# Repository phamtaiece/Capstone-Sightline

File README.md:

Hello everyone, 
This Github is for our capstone project " Plug and Play Visual Landing Aid Accessory for UAVs." 

Let's have fun together.

              ********************************************************************************************
04/03/2019

Kimball will have a meeting with Sightline hardware team to discuss about the layout and make some adjustments. We expect to have a physical board soon.

Tai will work on the test plan for circuit board, clean and update the Github site. 

There are some changes in plan that we decided to change to Mission Planner and use flight simulation rather than physical quadcopter. Then, we will try use SLA-1500 hardware to communicate with the simulation model using serial communication.

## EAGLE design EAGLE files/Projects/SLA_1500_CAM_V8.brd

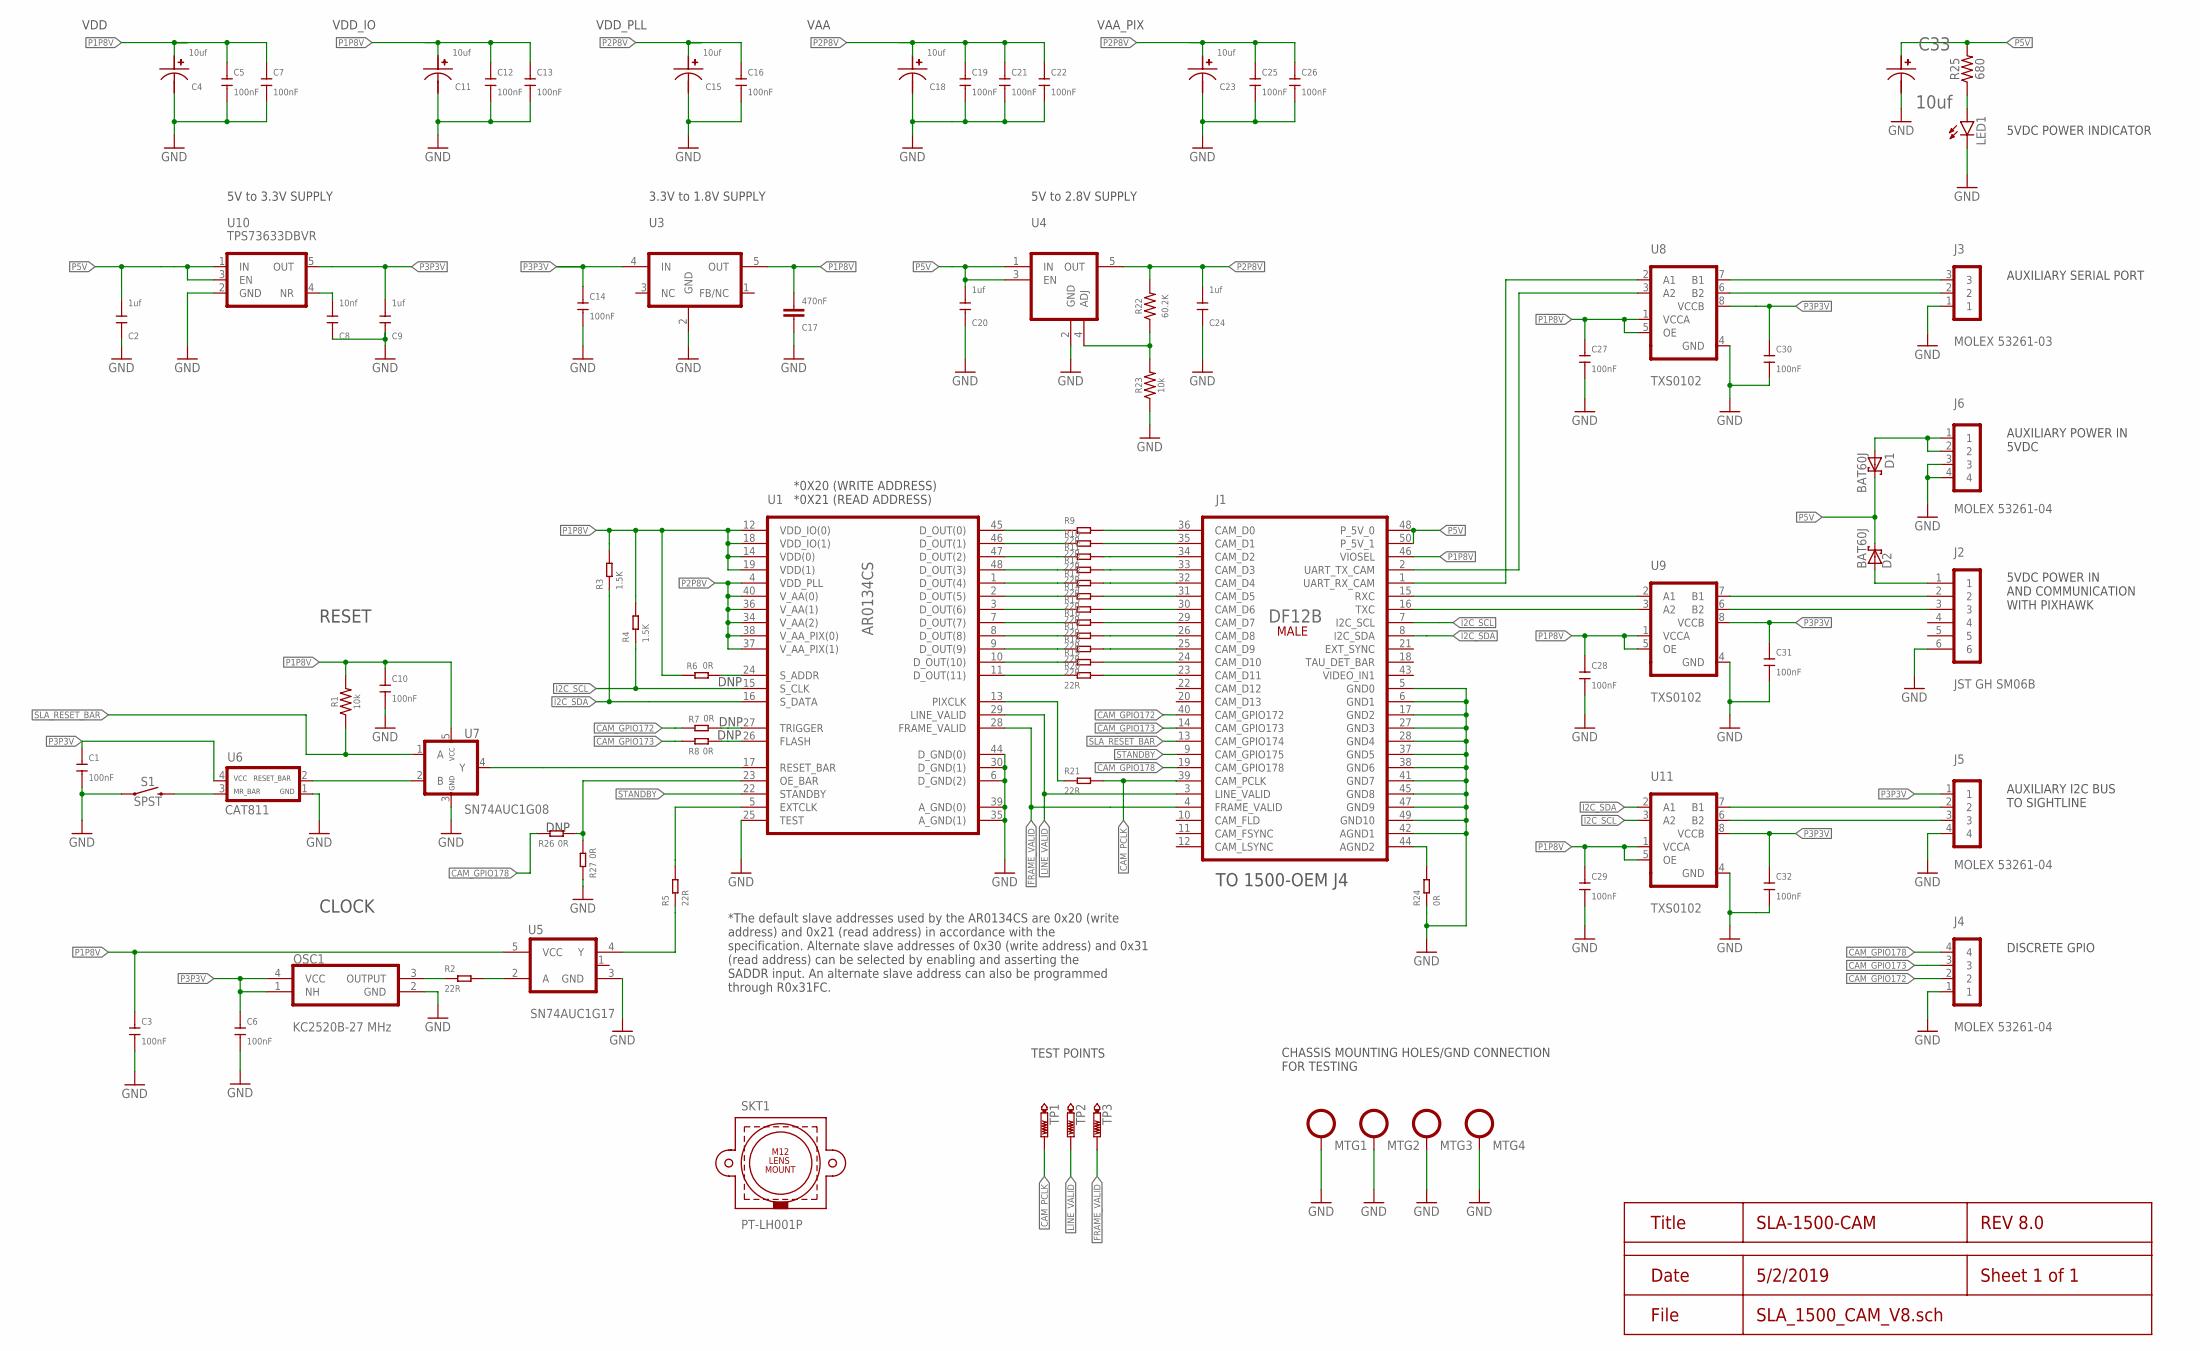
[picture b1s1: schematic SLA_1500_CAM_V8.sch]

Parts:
C1, C3, C5, C6, C7, C10, C12, C13, C14, C16, C19, C21, C22, C25, C26, C27, C28, C29, C30, C31, C32: 100nF; C0402
C2, C9, C20, C24: 1uf; C0402
C4, C11, C15, C18, C23, C33: 10uf; 0402
C8: 10nf; C0402
C17: 470nF; 0402
D1, D2: BAT60J; SOD323_ST
J1: DF12B(5.0)-50DS-0.5(86)SMT; DF12B(5.0)-50DS-0.5V(86)
J2: JST GH SM06B; JST_SM06B-GHS-TB
J3: MOLEX 53261-03; 53261-03
J4, J5, J6: MOLEX 53261-04; 53261-04
LED1: LEDCHIP-LED0603; CHIP-LED0603
MTG1, MTG2, MTG3, MTG4: SLA_MOUNTING
OSC1: KC2520B-27MHZ; 2.5X2.0_SMDCRYSTAL
R1, R23: 10k; 0603
R2, R5, R9, R10, R11, R12, R13, R14, R15, R16, R17, R18, R19, R20, R21: 22R; R0402
R3, R4: 1.5K; R0402
R6, R7, R8, R24, R26, R27: 0R; R0402
R22: 60.2K; 0603
R25: 680; 0603
S1: SPST; TACTILE_SWITCH_SMD_4.6X2.8MM
SKT1: PT-LH001P; M12_HOLDER
TP1, TP2, TP3: PTR1TP08SQ; TP08SQ
U1: AR0134CS-ILCC48; ILCC48_KD
U3: TPS71518DCKR; TI-SC70-5
U4: AP7331-WG-7; SOT-25
U5: SN74AUC1G17; SOT23-5
U6: CAT811; SOT-143-4
U7: SN74AUC1G08; SOT23-5
U8, U9, U11: TXS0102; X2SON(8)1.8X1.2MM
U10: TPS73633DBVR; SOT23-5

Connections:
CAM_GPIO172: J1.40 (CAM_GPIO172), J4.2, R7.2
CAM_GPIO173: J1.14 (CAM_GPIO173), J4.3, R8.2
CAM_GPIO178: J1.19 (CAM_GPIO178), J4.4, R26.2
CAM_PCLK: J1.39 (CAM_PCLK), R21.2, TP1.TP
FRAME_VALID: J1.4 (FRAME_VALID), TP3.TP, U1.28 (FRAME_VALID)
GND: C1.1, C2.1, C3.1, C4.2, C5.1, C6.1, C7.1, C8.1, C9.1, C10.1, C11.2, C12.1, C13.1, C14.1, C15.2, C16.1, C17.2, C18.2, C19.1, C20.1, C21.1, C22.1, C23.2, C24.1, C25.1, C26.1, C27.1, C28.1, C29.1, C30.1, C31.1, C32.1, C33.2, J1.5 (GND0), J1.6 (GND1), J1.17 (GND2), J1.27 (GND3), J1.28 (GND4), J1.37 (GND5), J1.38 (GND6), J1.41 (GND7), J1.42 (AGND1), J1.45 (GND8), J1.47 (GND9), J1.49 (GND10), J2.6, J3.1, J4.1, J5.4, J6.3, J6.4, LED1.C, MTG1.P$1, MTG2.P$1, MTG3.P$1, MTG4.P$1, OSC1.2 (GND), R23.1, R24.1, R27.2, S1.1, S1.2 (1), U1.6 (D_GND(2)), U1.25 (TEST), U1.30 (D_GND(1)), U1.35 (A_GND(1)), U1.39 (A_GND(0)), U1.44 (D_GND(0)), U3.2 (GND), U4.2 (GND), U5.3 (GND), U6.1 (GND), U7.3 (GND), U8.4 (GND), U9.4 (GND), U10.2 (GND), U11.4 (GND)
I2C_SCL: J1.7 (I2C_SCL), R4.1, U1.15 (S_CLK), U11.3 (A2)
I2C_SDA: J1.8 (I2C_SDA), R3.1, U1.16 (S_DATA), U11.2 (A1)
LINE_VALID: J1.3 (LINE_VALID), TP2.TP, U1.29 (LINE_VALID)
unnamed: J2.3, U9.6 (B2)
unnamed: R9.1, U1.45 (D_OUT(0))
unnamed: J1.36 (CAM_D0), R9.2
unnamed: R10.1, U1.46 (D_OUT(1))
unnamed: J1.35 (CAM_D1), R10.2
unnamed: R11.1, U1.47 (D_OUT(2))
unnamed: J1.34 (CAM_D2), R11.2
unnamed: R12.1, U1.48 (D_OUT(3))
unnamed: J1.33 (CAM_D3), R12.2
unnamed: R13.1, U1.1 (D_OUT(4))
unnamed: J1.32 (CAM_D4), R13.2
unnamed: R14.1, U1.2 (D_OUT(5))
unnamed: J3.3, U8.7 (B1)
unnamed: J1.31 (CAM_D5), R14.2
unnamed: R2.2, U5.2 (A)
unnamed: OSC1.3 (OUTPUT), R2.1
unnamed: J2.2, U9.7 (B1)
unnamed: J3.2, U8.6 (B2)
unnamed: J1.1 (UART_RX_CAM), U8.2 (A1)
unnamed: J1.2 (UART_TX_CAM), U8.3 (A2)
unnamed: C8.2, U10.4 (NR)
unnamed: R15.1, U1.3 (D_OUT(6))
unnamed: R22.1, R23.2, U4.4 (ADJ)
unnamed: J1.30 (CAM_D6), R15.2
unnamed: R5.1, U5.4 (Y)
unnamed: R5.2, U1.5 (EXTCLK)
unnamed: S1.3 (2), S1.4 (2), U6.3 (MR_BAR)
unnamed: U6.2 (RESET_BAR), U7.2 (B)
unnamed: U1.17 (RESET_BAR), U7.4 (Y)
unnamed: LED1.A, R25.1
unnamed: J1.44 (AGND2), R24.2
unnamed: R7.1, U1.27 (TRIGGER)
unnamed: R8.1, U1.26 (FLASH)
unnamed: D2.A, J2.1
unnamed: J1.15 (RXC), U9.2 (A1)
unnamed: J1.16 (TXC), U9.3 (A2)
unnamed: J5.2, U11.7 (B1)
unnamed: J5.3, U11.6 (B2)
unnamed: D1.A, J6.1, J6.2
unnamed: R16.1, U1.7 (D_OUT(7))
unnamed: J1.29 (CAM_D7), R16.2
unnamed: R17.1, U1.8 (D_OUT(8))
unnamed: J1.26 (CAM_D8), R17.2
unnamed: R18.1, U1.9 (D_OUT(9))
unnamed: J1.25 (CAM_D9), R18.2
unnamed: R19.1, U1.10 (D_OUT(10))
unnamed: J1.24 (CAM_D10), R19.2
unnamed: R20.1, U1.11 (D_OUT(11))
unnamed: J1.23 (CAM_D11), R20.2
unnamed: R26.1, R27.1, U1.23 (OE_BAR)
unnamed: R6.1, U1.24 (S_ADDR)
P1P8V: C3.2, C4.1, C5.2, C7.2, C10.2, C11.1, C12.2, C13.2, C17.1, C27.2, C28.2, C29.2, J1.46 (VIOSEL), R1.2, R3.2, R4.2, R6.2, U1.12 (VDD_IO(0)), U1.14 (VDD(0)), U1.18 (VDD_IO(1)), U1.19 (VDD(1)), U3.5 (OUT), U5.5 (VCC), U7.5 (VCC), U8.1 (VCCA), U8.5 (OE), U9.1 (VCCA), U9.5 (OE), U11.1 (VCCA), U11.5 (OE)
P2P8V: C15.1, C16.2, C18.1, C19.2, C21.2, C22.2, C23.1, C24.2, C25.2, C26.2, R22.2, U1.4 (VDD_PLL), U1.34 (V_AA(2)), U1.36 (V_AA(1)), U1.37 (V_AA_PIX(1)), U1.38 (V_AA_PIX(0)), U1.40 (V_AA(0)), U4.5 (OUT)
P3P3V: C1.2, C6.2, C9.2, C14.2, C30.2, C31.2, C32.2, J5.1, OSC1.1 (NH), OSC1.4 (VCC), U3.4 (IN), U6.4 (VCC), U8.8 (VCCB), U9.8 (VCCB), U10.5 (OUT), U11.8 (VCCB)
P5V: C2.2, C20.2, C33.1, D1.C, D2.C, J1.48 (P_5V_0), J1.50 (P_5V_1), R25.2, U4.1 (IN), U4.3 (EN), U10.1 (IN), U10.3 (EN)
PIXCLK: R21.1, U1.13 (PIXCLK)
SLA_RESET_BAR: J1.13 (CAM_GPIO174), R1.1, U7.1 (A)
STANDBY: J1.9 (CAM_GPIO175), U1.22 (STANDBY)

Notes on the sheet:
AUXILIARY POWER IN 5VDC
AUXILIARY I2C BUS TO SIGHTLINE
DISCRETE GPIO
5VDC POWER IN AND COMMUNICATION WITH PIXHAWK
AUXILIARY SERIAL PORT
5V to 3.3V SUPPLY
3.3V to 1.8V SUPPLY
5V to 2.8V SUPPLY
TO 1500-OEM J4
DNP
5VDC POWER INDICATOR
*The default slave addresses used by the AR0134CS are 0x20 (write address) and 0x21 (read address) in accordance with the specification. Alternate slave addresses of 0x30 (write address) and 0x31 (read address) can be selected by enabling and asserting the SADDR input. An alternate slave address ca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
*0X20 (WRITE ADDRESS) *0X21 (READ ADDRESS)
CHASSIS MOUNTING HOLES/GND CONNECTION FOR TESTING
TEST POINTS
CLOCK
RESET
VDD
VDD_PLL
VAA
VAA_PIX
VDD_IO

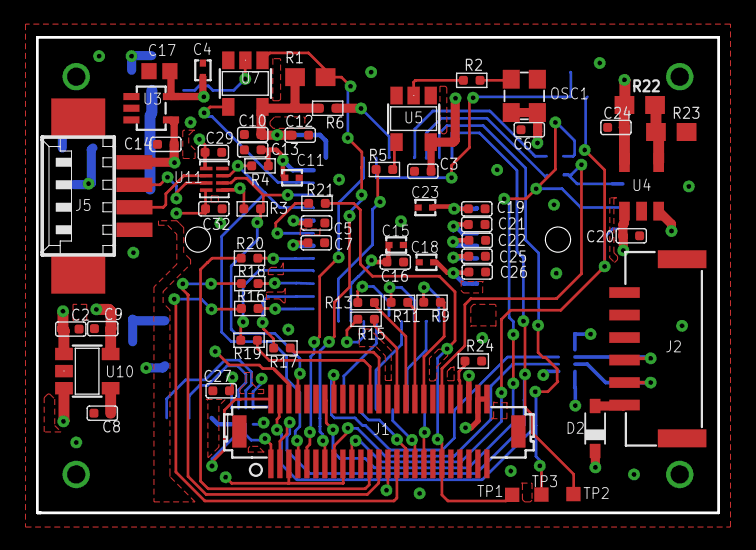
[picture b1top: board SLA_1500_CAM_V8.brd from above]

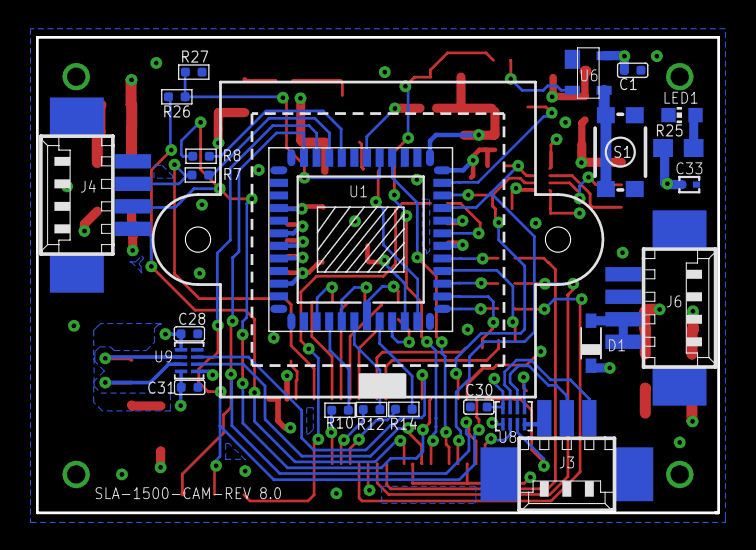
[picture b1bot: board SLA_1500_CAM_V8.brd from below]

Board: 4 copper layers, 37.8 x 26.4 mm, 89 parts (24 on the bottom side), 67 nets.

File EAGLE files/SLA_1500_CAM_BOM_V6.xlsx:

Qty | Value | Device | Package | Parts | Description | DESCRIPTION.1 | MANF | MANF# | MPN | PROD_ID | TP_SIGNAL_NAME | VALUE.1 | Column1
1 |  | AP7331-WG-7 | SOT-25 | U4 | AP7331-WG-7 | 300mA, LOW QUIESCENT CURRENT, FAST TRANSIENT LOW DROPOUT LINEAR REGULATOR, ADJU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 | DIODES INCORPORATED | AP7331-WG-7
1 |  | AR0134CS-ILCC48 | ILCC48_KD | U1 | AR0134CS-1LCC48-10x10 | 1/3-inch 1.2 Mp CMOS digital image sensor with an active-pixel array of 1280 (H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 | On Semiconductor | AR0134CSSM00SPCA0
1 |  | CAT811 | SOT-143-4 | U6 | CAT811-SOT-143-4 | IC, SUPERVISOR, MICROPROCESSOR POWER SUPPLY, 2.93V, ACTIVE LOW RESET, SOT143-4 | On Semiconductor | CAT811STBI
1 |  | DF12B(5.0)-50DS-0.5(86)SMT | DF12B(5.0)-50DS-0.5V(86) | J1 | DF12B(5.0)-50DS-0.5(86) | DF12B-50DS-0.5V(86) Hirose Male 50-pin connector | Hirose | 537-0309-6 86
1 |  | KC2520B-27MHZ | 2.5X2.0_SMDCRYSTAL | OSC1 | KC2520B-27MHz-2.5X2.0 | OSC, CRYSTAL CLOCK, SMD, CMOS, 2.25V TO 3.63V, 4mA, 27.0000MHz, 2.5MM x 2.0MM | Kyocera | KC2520B27.0000C2GE00
1 |  | LEDCHIP-LED0603 | CHIP-LED0603 | LED1 | LED
4 |  | SLA_MOUNTING | SLA_MOUNTING | MTG1, MTG2, MTG3, MTG4
1 |  | SN74AUC1G08 | SOT23-5 | U7 | SN74AUC1G08-SOT23-5 | IC, AND GATE, SINGLE, 2 INPUT POSITIVE, SGL, SOT23-5 | Texas Instruments | SN74AUC1G08DBVR
1 |  | SN74AUC1G17 | SOT23-5 | U5 | SN74AUC1G17-SOT23-5 | IC, BUFFER, SINGLE SCHMITT-TRIGGER, 9mA, 0.8V TO 2.7V, SOT23-5 | TEXAS INSTRUMENTS | SN74AUC1G17DBV
1 |  | TPS71518DCKR | TI-SC70-5 | U3 | TPS71518DCKR | 50-mA, 24-V, 3.2-Î¼A Supply Current Low-Dropout Linear Regulator in SC70 5-Pin 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 | TEXAS INSTRUMENTS | TPS71518DCKR
4 | 0R | SMD-RES-0R-5%-1/16W(0402) | R0402 | R6, R7, R8, R24 | 301010000 |  |  |  | RC0402JR-070RL |  |  | 0R
2 | 1.5K | SMD-RES-1.5K-5%-1/16W(0402) | R0402 | R3, R4 | 301010001 |  |  |  | RC0402JR-071K5L |  |  | 1.5K
21 | 100nF | CERAMICÂ 100NF-10V-10%-X5R(0402) | C0402 | C1, C3, C5, C6, C7, C10, C12, C13, C14, C16, C19, C21, C22, C25, C26, C27, C28,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 | 302010037 |  |  |  | CC0402KRX5R6BB104 |  |  | 100NF 10V
2 | 10k | 10KOHM-0603-1/10W-1% | 0603 | R1, R23 | 10kÎ© resistor |  |  |  |  | RES-00824 |  | 10k
1 | 10nf | CERAMIC-10NF-50V-10%-X7R(0402) | C0402 | C8 | 302010006 |  |  |  | CC0402KRX7R9BB103 |  |  | 10nf
5 | 10uf | F980G106MUA | 0402 | C4, C11, C15, C18, C23 | F980G106MUA | Tantalum Capacitors - Solid SMD 10uF 4V 20% 0402, 1.1x0.6x0.35mm | AVX | F980G106MUA
1 | 10uf | F980J106MUALZT | 0402 | C33 | F980G106MUALZT | Tantalum Capacitors - Solid SMD 10uF 6.3V 20% 0402, 1.1x0.6x0.35mm | AVX | F980J106MUALZT
4 | 1uf | CERAMIC-1UF-10V-10%-X5R(0402) | C0402 | C2, C9, C20, C24 | 302010040 |  |  |  | CC0402KRX5R6BB105 |  |  | 1uf
15 | 22R | SMD-RES-22R-1%-1/16W(0402) | R0402 | R2, R5, R9, R10, R11, R12, R13, R14, R15, R16, R17, R18, R19, R20, R21 | 301010052 |  |  |  | RC0402FR-0722RL |  |  | 22R
1 | 470nF | 470NF-0402-16V-10% | 0402 | C17 | 0.47uF/470nF ceramic capacitors |  |  |  |  | CAP-09041 |  | 470nF
1 | 60.2K | 62KOHM-0603-1/10W-5% | 0603 | R22 | 62kÎ© resistor
1 | 680 | 680OHM-0603-1/10W-5% | 0603 | R25 | 680Î© resistor |  |  |  |  | RES-09333 |  | 680
2 | BAT60J | BAT60J | SOD323_ST | D1, D2 | Schottky barrier diode
1 | JST GH SM06B | JST_GH_SM06B-GHS-TB | JST_SM06B-GHS-TB | J2 | JST SM06B-GHS-TB | 1.25 MM SIDE-ENTRY 6-PIN SMT CONNECTOR | JST | SM06B-GHS-TB
1 | MOLEX 53261-03 | MOLEX53261-03 | 53261-03 | J3 | MOLEX 53261-03 | 1.25mm Pitch PicoBlade Header, Surface Mount, Right-Angle, 3 Circuits, Tin (Sn)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 | MOLEX | 532610371
3 | MOLEX 53261-04 | MOLEX53261-04 | 53261-04 | J4, J5, J6 | MOLEX 53261-04 | 1.25mm Pitch PicoBlade Header, Surface Mount, Right-Angle, 4 Circuits, Tin (Sn)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 | MOLEX | 532610471
1 | PT-LH001P | M12_LENS_MOUNT | M12_HOLDER | SKT1 | PT-LH001P | PT-LH001P Plastic M12 Lens Holder, 20mm Hole Spacing | M12 LENSES | PT-LH001P
3 | PTR1TP08SQ | PTR1TP08SQ | TP08SQ | TP1, TP2, TP3 | TEST PIN
1 | SPST | MOMENTARY-SWITCH-SPST-SMD-4.6X2.8MM | TACTILE_SWITCH_SMD_4.6X2.8MM | S1 | Momentary Switch (Pushbutton) - SPST |  |  |  |  | SWCH-13065
1 | TPS73633DBVR | TPS73633DBVR | SOT23-5 | U10 | TPS73633DBVR | Cap-Free, NMOS, 400-mA Low-Dropout Regulator with Reverse Current Protection 5.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 | Texas Instruments | TPS73633DBVR
3 | TXS0102 | TXS0102DQM | X2SON(8)1.8X1.2MM | U8, U9, U11 | TXS0102DQM 1.8 X 1.2 mm | TXS0102 2-Bit Bidirectional Voltage-Level Translator for Open-Drain and Push-Pu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 | Texas Instruments | TXS0102DQM

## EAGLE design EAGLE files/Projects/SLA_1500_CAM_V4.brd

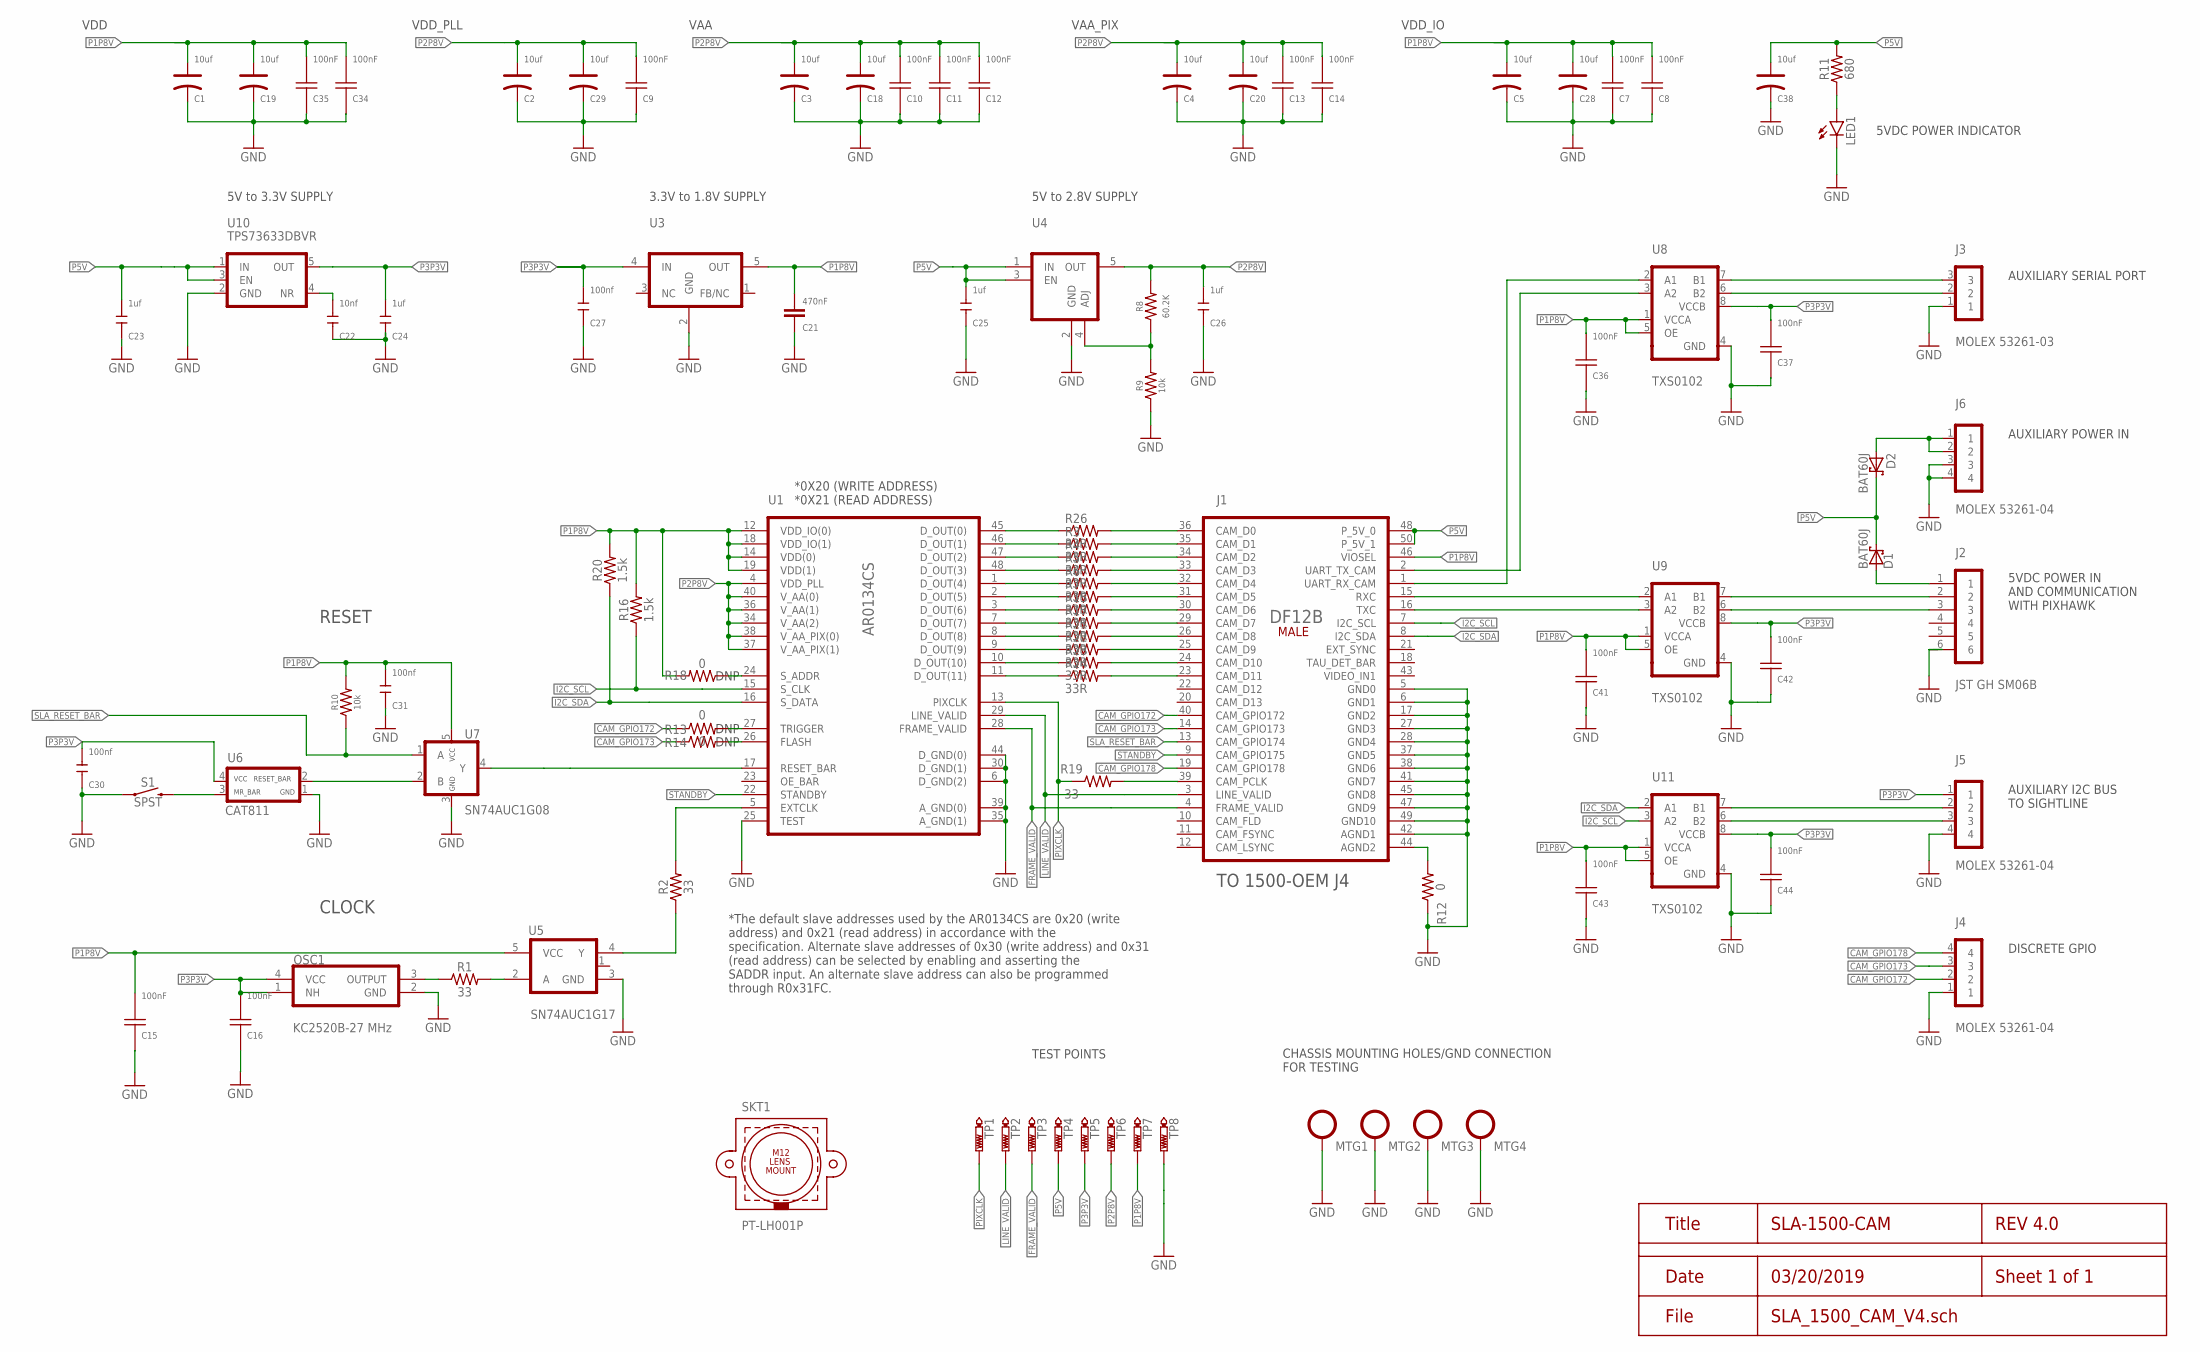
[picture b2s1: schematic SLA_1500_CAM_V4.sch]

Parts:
C1, C2, C3, C4, C5, C18, C19, C20, C28, C29, C38: 10uf; AVX-A
C7, C8, C9, C10, C11, C12, C13, C14, C15, C16, C34, C35, C36, C37, C41, C42, C43, C44: CAP0201100NF; R0201
C21: 470nF; 0402
C22: 10nf; C0402
C23, C24, C25, C26: 1uf; C0402
C27, C30, C31: 100nf; C0402
D1, D2: BAT60J; SOD323_ST
J1: DF12B(5.0)-50DS-0.5(86)SMT; DF12B(5.0)-50DS-0.5V(86)
J2: JST GH SM06B; JST_SM06B-GHS-TB
J3: MOLEX 53261-03; 53261-03
J4, J5, J6: MOLEX 53261-04; 53261-04
LED1: LEDCHIP-LED0603; CHIP-LED0603
MTG1, MTG2, MTG3, MTG4: SLA_MOUNTING
OSC1: KC2520B-27MHZ; 2.5X2.0_SMDCRYSTAL
R1, R2, R19: 33; 0402
R3, R4, R5, R6, R7, R15, R17, R21, R22, R23, R24, R26: 33R; R0201
R8: 60.2K; 0603
R9, R10: 10k; 0603
R11: 680; 0603
R12, R13, R14, R18: 0; 0402
R16, R20: 1.5k; 0603
S1: SPST; TACTILE_SWITCH_SMD_4.6X2.8MM
SKT1: PT-LH001P; M12_HOLDER
TP1, TP2, TP3, TP4, TP5, TP6, TP7, TP8: PTR1PAD1-13; P1-13
U1: AR0134CS-ILCC48; ILCC48_KD
U3: TPS71518DCKR; TI-SC70-5
U4: AP7331-WG-7; SOT-25
U5: SN74AUC1G17; SOT23-5
U6: CAT811; SOT-143-4
U7: SN74AUC1G08; SOT23-5
U8, U9, U11: TXS0102; X2SON(8)1.8X1.2MM
U10: TPS73633DBVR; SOT23-5

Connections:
CAM_GPIO172: J1.40 (CAM_GPIO172), J4.2, R13.1
CAM_GPIO173: J1.14 (CAM_GPIO173), J4.3, R14.1
CAM_GPIO178: J1.19 (CAM_GPIO178), J4.4
FRAME_VALID: J1.4 (FRAME_VALID), TP3.TP, U1.28 (FRAME_VALID)
GND: C1.-, C2.-, C3.-, C4.-, C5.-, C7.2, C8.2, C9.2, C10.2, C11.2, C12.2, C13.2, C14.2, C15.2, C16.2, C18.-, C19.-, C20.-, C21.2, C22.1, C23.1, C24.1, C25.1, C26.1, C27.1, C28.-, C29.-, C30.1, C31.1, C34.2, C35.2, C36.2, C37.2, C38.-, C41.2, C42.2, C43.2, C44.2, J1.5 (GND0), J1.6 (GND1), J1.17 (GND2), J1.27 (GND3), J1.28 (GND4), J1.37 (GND5), J1.38 (GND6), J1.41 (GND7), J1.42 (AGND1), J1.45 (GND8), J1.47 (GND9), J1.49 (GND10), J2.6, J3.1, J4.1, J5.4, J6.3, J6.4, LED1.C, MTG1.P$1, MTG2.P$1, MTG3.P$1, MTG4.P$1, OSC1.2 (GND), R9.1, R12.1, S1.1, S1.2 (1), TP8.TP, U1.6 (D_GND(2)), U1.25 (TEST), U1.30 (D_GND(1)), U1.35 (A_GND(1)), U1.39 (A_GND(0)), U1.44 (D_GND(0)), U3.2 (GND), U4.2 (GND), U5.3 (GND), U6.1 (GND), U7.3 (GND), U8.4 (GND), U9.4 (GND), U10.2 (GND), U11.4 (GND)
I2C_SCL: J1.7 (I2C_SCL), R16.1, U1.15 (S_CLK), U11.3 (A2)
I2C_SDA: J1.8 (I2C_SDA), R20.1, U1.16 (S_DATA), U11.2 (A1)
LINE_VALID: J1.3 (LINE_VALID), TP2.TP, U1.29 (LINE_VALID)
unnamed: J2.3, U9.6 (B2)
unnamed: R26.1, U1.45 (D_OUT(0))
unnamed: J1.36 (CAM_D0), R26.2
unnamed: R3.1, U1.46 (D_OUT(1))
unnamed: J1.35 (CAM_D1), R3.2
unnamed: R4.1, U1.47 (D_OUT(2))
unnamed: J1.34 (CAM_D2), R4.2
unnamed: R5.1, U1.48 (D_OUT(3))
unnamed: J1.33 (CAM_D3), R5.2
unnamed: R6.1, U1.1 (D_OUT(4))
unnamed: J1.32 (CAM_D4), R6.2
unnamed: R7.1, U1.2 (D_OUT(5))
unnamed: J3.3, U8.7 (B1)
unnamed: J1.31 (CAM_D5), R7.2
unnamed: R1.2, U5.2 (A)
unnamed: OSC1.3 (OUTPUT), R1.1
unnamed: J2.2, U9.7 (B1)
unnamed: J3.2, U8.6 (B2)
unnamed: J1.1 (UART_RX_CAM), U8.2 (A1)
unnamed: J1.2 (UART_TX_CAM), U8.3 (A2)
unnamed: C22.2, U10.4 (NR)
unnamed: R15.1, U1.3 (D_OUT(6))
unnamed: R8.1, R9.2, U4.4 (ADJ)
unnamed: J1.30 (CAM_D6), R15.2
unnamed: R2.1, U5.4 (Y)
unnamed: R2.2, U1.5 (EXTCLK)
unnamed: S1.3 (2), S1.4 (2), U6.3 (MR_BAR)
unnamed: U6.2 (RESET_BAR), U7.2 (B)
unnamed: U1.17 (RESET_BAR), U7.4 (Y)
unnamed: LED1.A, R11.1
unnamed: J1.44 (AGND2), R12.2
unnamed: R13.2, U1.27 (TRIGGER)
unnamed: R14.2, U1.26 (FLASH)
unnamed: D1.A, J2.1
unnamed: J1.15 (RXC), U9.2 (A1)
unnamed: J1.16 (TXC), U9.3 (A2)
unnamed: J5.2, U11.7 (B1)
unnamed: J5.3, U11.6 (B2)
unnamed: D2.A, J6.1, J6.2
unnamed: R17.1, U1.7 (D_OUT(7))
unnamed: J1.29 (CAM_D7), R17.2
unnamed: R21.1, U1.8 (D_OUT(8))
unnamed: J1.26 (CAM_D8), R21.2
unnamed: R22.1, U1.9 (D_OUT(9))
unnamed: J1.25 (CAM_D9), R22.2
unnamed: R23.1, U1.10 (D_OUT(10))
unnamed: J1.24 (CAM_D10), R23.2
unnamed: R24.1, U1.11 (D_OUT(11))
unnamed: J1.23 (CAM_D11), R24.2
unnamed: R18.1, U1.24 (S_ADDR)
unnamed: J1.39 (CAM_PCLK), R19.2
P1P8V: C1.+, C5.+, C7.1, C8.1, C15.1, C19.+, C21.1, C28.+, C31.2, C34.1, C35.1, C36.1, C41.1, C43.1, J1.46 (VIOSEL), R10.2, R16.2, R18.2, R20.2, TP7.TP, U1.12 (VDD_IO(0)), U1.14 (VDD(0)), U1.18 (VDD_IO(1)), U1.19 (VDD(1)), U3.5 (OUT), U5.5 (VCC), U7.5 (VCC), U8.1 (VCCA), U8.5 (OE), U9.1 (VCCA), U9.5 (OE), U11.1 (VCCA), U11.5 (OE)
P2P8V: C2.+, C3.+, C4.+, C9.1, C10.1, C11.1, C12.1, C13.1, C14.1, C18.+, C20.+, C26.2, C29.+, R8.2, TP6.TP, U1.4 (VDD_PLL), U1.34 (V_AA(2)), U1.36 (V_AA(1)), U1.37 (V_AA_PIX(1)), U1.38 (V_AA_PIX(0)), U1.40 (V_AA(0)), U4.5 (OUT)
P3P3V: C16.1, C24.2, C27.2, C30.2, C37.1, C42.1, C44.1, J5.1, OSC1.1 (NH), OSC1.4 (VCC), TP5.TP, U3.4 (IN), U6.4 (VCC), U8.8 (VCCB), U9.8 (VCCB), U10.5 (OUT), U11.8 (VCCB)
P5V: C23.2, C25.2, C38.+, D1.C, D2.C, J1.48 (P_5V_0), J1.50 (P_5V_1), R11.2, TP4.TP, U4.1 (IN), U4.3 (EN), U10.1 (IN), U10.3 (EN)
PIXCLK: R19.1, TP1.TP, U1.13 (PIXCLK)
SLA_RESET_BAR: J1.13 (CAM_GPIO174), R10.1, U7.1 (A)
STANDBY: J1.9 (CAM_GPIO175), U1.22 (STANDBY)

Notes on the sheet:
AUXILIARY POWER IN
AUXILIARY I2C BUS TO SIGHTLINE
DISCRETE GPIO
5VDC POWER IN AND COMMUNICATION WITH PIXHAWK
AUXILIARY SERIAL PORT
5V to 3.3V SUPPLY
3.3V to 1.8V SUPPLY
5V to 2.8V SUPPLY
TO 1500-OEM J4
DNP
5VDC POWER INDICATOR
*The default slave addresses used by the AR0134CS are 0x20 (write address) and 0x21 (read address) in accordance with the specification. Alternate slave addresses of 0x30 (write address) and 0x31 (read address) can be selected by enabling and asserting the SADDR input. An alternate slave address ca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
*0X20 (WRITE ADDRESS) *0X21 (READ ADDRESS)
CHASSIS MOUNTING HOLES/GND CONNECTION FOR TESTING
TEST POINTS
CLOCK
RESET
VDD
VDD_PLL
VAA
VAA_PIX
VDD_IO

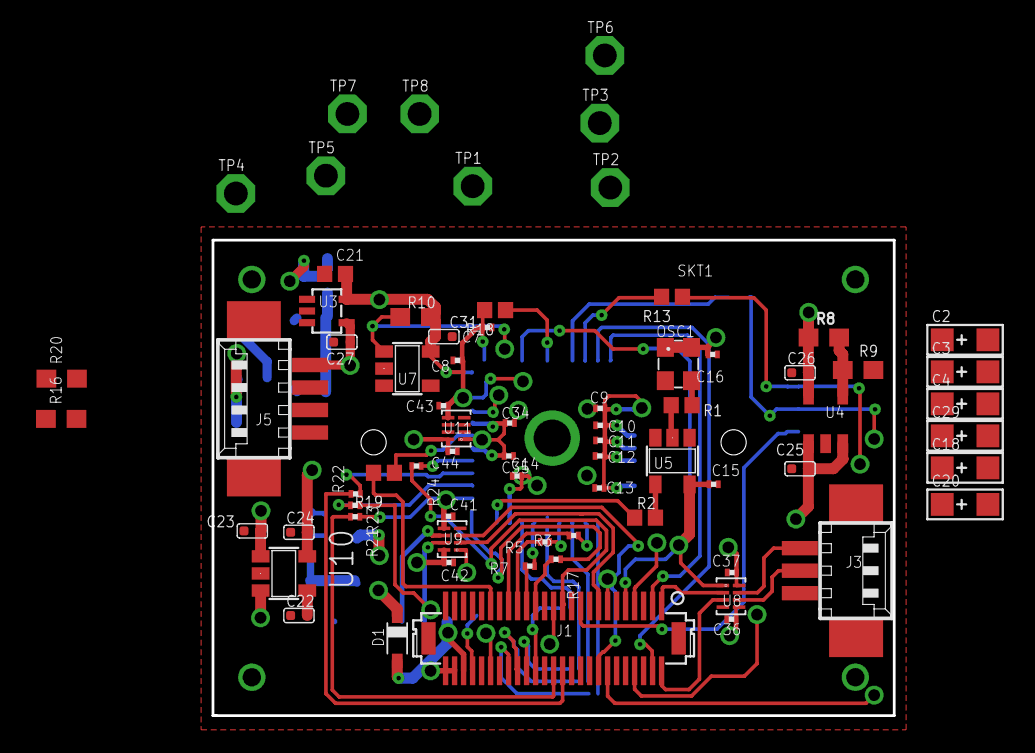
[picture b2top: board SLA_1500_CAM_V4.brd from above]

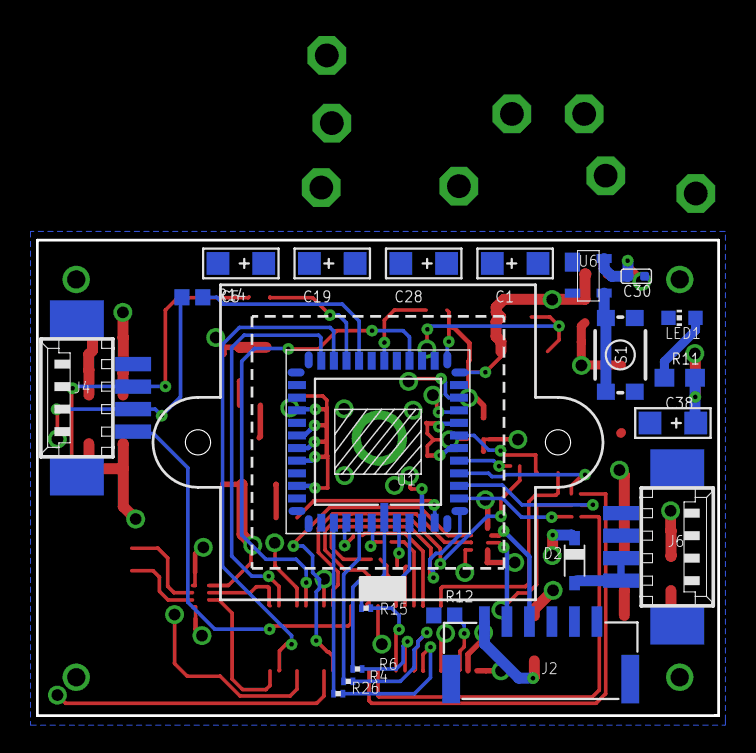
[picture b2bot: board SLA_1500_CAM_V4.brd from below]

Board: 4 copper layers, 37.8 x 26.4 mm, 97 parts (22 on the bottom side), 66 nets.

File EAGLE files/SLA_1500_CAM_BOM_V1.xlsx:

Qty | Value | Device | Package | Parts | Description | DESCRIPTION.1 | MANF | MANF# | MPN | PROD_ID | VALUE.1 | Column1
1 |  | AP7331-WG-7 | SOT-25 | U4 | AP7331-WG-7 | 300mA, LOW QUIESCENT CURRENT, FAST TRANSIENT LOW DROPOUT LINEAR REGULATOR, ADJU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 | DIODES INCORPORATED | AP7331-WG-7
1 |  | AR0134CS-ILCC48 | ILCC48 | U1 | AR0134CS-1LCC48-10x10 | 1/3-inch 1.2 Mp CMOS digital image sensor with an active-pixel array of 1280 (H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 | On Semiconductor | AR0134CSSM00SPCA0
1 |  | CAT811 | SOT-143-4 | U6 | CAT811-SOT-143-4 | IC, SUPERVISOR, MICROPROCESSOR POWER SUPPLY, 2.93V, ACTIVE LOW RESET, SOT143-4 | On Semiconductor | CAT811STBI
1 |  | DF12B(5.0)-50DS-0.5(86)SMT | DF12B(5.0)-50DS-0.5V(86) | J1 | DF12B(5.0)-50DS-0.5(86) | DF12B-50DS-0.5V(86) Hirose Male 50-pin connector | Hirose | 537-0309-6 86
1 |  | JST_GH_SM06B-GHS-TB | JST_SM06B-GHS-TB | J2 | JST SM06B-GHS-TB | 1.25 MM SIDE-ENTRY 6-PIN SMT CONNECTOR | JST | SM06B-GHS-TB
1 |  | KC2520B-27MHZ | 2.5X2.0_SMDCRYSTAL | OSC1 | KC2520B-27MHz-2.5X2.0 | OSC, CRYSTAL CLOCK, SMD, CMOS, 2.25V TO 3.63V, 4mA, 27.0000MHz, 2.5MM x 2.0MM | Kyocera | KC2520B27.0000C2GE00
1 |  | LEDCHIP-LED0603 | CHIP-LED0603 | LED1 | LED
1 |  | MOLEX_53048-03 | 53048-03 | J3 |  | MOLEX 53048-03 3-PIN CONNECTOR | MOLEX | 53048-0310
2 |  | MOLEX_53398-04 | 53398-04 | J4, J6 |  | MOLEX 53398-04 4-PIN SMT CONNECTOR | MOLEX | 53398-0471
1 |  | SN74AUC1G08 | SOT23-5 | U7 | SN74AUC1G08-SOT23-5 | IC, AND GATE, SINGLE, 2 INPUT POSITIVE, SGL, SOT23-5 | Texas Instruments | SN74AUC1G08DBVR
1 |  | SN74AUC1G17 | SOT23-5 | U5 | SN74AUC1G17-SOT23-5 | IC, BUFFER, SINGLE SCHMITT-TRIGGER, 9mA, 0.8V TO 2.7V, SOT23-5 | TEXAS INSTRUMENTS | SN74AUC1G17DBV
1 |  | TPS71518DCKR | TI-SC70-5 | U3 | TPS71518DCKR | 50-mA, 24-V, 3.2-Î¼A Supply Current Low-Dropout Linear Regulator in SC70 5-Pin 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 | TEXAS INSTRUMENTS | TPS71518DCKR
1 |  | TPS73633DCQR | SOT-223-6-PIN | U2 | TPS73633DCQR | Cap-Free, NMOS, 400-mA Low-Dropout Regulator with Reverse Current Protection 5.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 | TEXAS INSTRUMENTS | TPS73633DCQR
5 | 0 | RESISTOR0402 | 0402 | R3, R4, R5, R6, R7 | Generic Resistor Package
12 | 100nf | CAP0201100NF | R0201 | C6, C7, C8, C9, C10, C11, C12, C13, C14, C15, C16, C17 | CAP0201 PANASONIC CERAMIC CAPACITOR | CAP, CERAMIC, 100nF, 10V, X5R, 20%, 0201 | PANASONIC | ECJZEB1A104M
3 | 100nf | CERAMIC-100NF-25V-10%-X7R(0402) | C0402 | C27, C30, C31 | 302010024 |  |  |  | CC0402KRX7R8BB104 |  | 100nf
2 | 10k | 10KOHM-0603-1/10W-1% | 0603 | R9, R10 | 10kÎ© resistor |  |  |  |  | RES-00824 | 10k
1 | 10nf | CERAMIC-10NF-50V-10%-X7R(0402) | C0402 | C22 | 302010006 |  |  |  | CC0402KRX7R9BB103 |  | 10nf
10 | 10uf | TANTALUM-SMD-10UF-10V-10%(AVX-A) | AVX-A | C1, C2, C3, C4, C5, C18, C19, C20, C28, C29 | 302020011 |  |  |  | TAJA106K010RNJ |  | 10uf
4 | 1uf | CERAMIC-1UF-10V-10%-X5R(0402) | C0402 | C23, C24, C25, C26 | 302010040 |  |  |  | CC0402KRX5R6BB105 |  | 1uf
2 | 33 | RESISTOR0402 | 0402 | R1, R2 | Generic Resistor Package
1 | 470nF | 470NF-0402-16V-10% | 0402 | C21 | 0.47uF/470nF ceramic capacitors |  |  |  |  | CAP-09041 | 470nF
1 | 60.2K | 62KOHM-0603-1/10W-5% | 0603 | R8 | 62kÎ© resistor
1 | 680 | 680OHM-0603-1/10W-5% | 0603 | R11 | 680Î© resistor |  |  |  |  | RES-09333 | 680
5 | JUMPER_NC | JUMPER-SMT_2_NC_TRACE_SILK | SMT-JUMPER_2_NC_TRACE_SILK | JP1, JP2, JP3, JP4, JP5 | Normally closed trace jumper
1 | MOLEX 53398-04 | MOLEX_53398-04 | 53398-04 | J5 |  | MOLEX 53398-04 4-PIN SMT CONNECTOR | MOLEX | 53398-0471
1 | SPST | MOMENTARY-SWITCH-SPST-SMD-4.6X2.8MM | TACTILE_SWITCH_SMD_4.6X2.8MM | S1 | Momentary Switch (Pushbutton) - SPST |  |  |  |  | SWCH-13065

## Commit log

2018-12-13 Added Google Drive docs
2018-12-15 Introduction and basic information about Pixhawk 4
    Pixhawk4 works best with PX4 autopilot and QgroundControll.
    The Docs provides a lot of essential information.
2018-12-18 Added quadcopter research doc
    Proposal 1
2018-12-20 Added Quadcopter Proposal II
2019-01-01 Added proposal 3, BOM, and datasheets
2019-01-02 Added Meeting Minutes
2019-01-03 Create Statement of Work
2019-01-03 Update and rename Statement of Work to General Documents/ Statements of Work
2019-01-05 Update and rename Statements of Work to Statements of Work
2019-01-05 Update Statements of Work
2019-01-06 Create Weekly Report
2019-01-07 Added Sightline_SOW.docx
2019-01-07 Added content to SOW
2019-01-07 Added content to SIGHTLINE_SOW.docx
2019-01-11 Tai 01/11/2019
2019-01-12 Update SIGHTLINE_SOW.docx
    Level 0 diagram V4
2019-01-13 Update SIGHTLINE_SOW.docx
    Added hardware requirements
2019-01-13 added WPR folder and doc
2019-01-14 Added AR0134 files
    AR0134 datasheet, BOMs from ONSemi, and BOM.xslx for capstone
2019-01-15 update Quadcopter BOM
    Included LiPo Battery charger, and addtional telemetry for ground control
2019-01-15 update Q&A
2019-01-16 Updated Q&A
2019-01-16 Update Quadcotper BOM
    Included fireproof LiPo bag
2019-01-16 Create SightLineSoftware
2019-01-16 NEW: SightLine Landing aid sample code
2019-01-16 DEL: too agressive with my checkin
2019-01-16 Added some bullet notes describing what you'll find in the SLALandingApp.
2019-01-16 added Interesting_Reading folder and Drone Comm and Command article from Circuit Cellar magazine
2019-01-21 Added DF12B documents
2019-01-22 Add DF12B docs
2019-01-22 SightLine documentation on itegrating video into QGroundControl
    This covers video streaming only. It does not cover command and control.
2019-01-26 Create Working_space
2019-01-27 Added Eagle Files .lbr and .sch
2019-01-28 SightLine setup instructions for Airborne Innovations camera (On-Semi sensor)
    Airborne Innovations makes a camera based on the On-Semi sensor chosen for this project. This camera and the reference design provided by On-Semi will be used to make a custom board. These software c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
2019-01-30 Added Pixhawk 4 Docs
2019-02-01 Added Bottom Plate Dimensions for F450
2019-02-05 added suggested connections doc
    Added suggested connections from Jeremy. Also renamed folder "Docs" to "Sightline Docs"
2019-02-05 Update SightLineSuggestedConnections.xlsx
    Added part # for JST connector
2019-02-06 Update Sightline.lbr
    Created JST GH 6 pin connector
2019-02-07 Update Sightline Project Working Space.docx
    Added instructions for charging Batteries using Tenergy TB6B balanced charger.
2019-02-13 added Eagle Schematic V1
2019-02-13 update AB_board_schem_V1
2019-02-14 NEW: photos related to the project
2019-02-15 Includes screenshots and additional step for GCS
2019-02-18 Create SLA_1500_CAM_V1 schem
    Renamed schematic AB_BOARD_V1 to SLA_1500_CAM_V1. Added IO
2019-02-18 Deleted AB_BOARD_V1 files
2019-02-18 Added Sightline documents
2019-02-18 Update SLA_1500_CAM schem
2019-02-18 Update SLA_1500_CAM schem
    Created Devices, symbols, and footprints for power management
2019-02-19 Added SLA_1500_CAM_v1 pdf
    Removed AB_Board_v1 png
2019-02-19 Added SLA_1500_CAM_BOM_V1
    Deleted AB_BOARD_BOM
2019-02-25 Update Capstone_Quadcopter_Bill of Materials.xlsx
    Added replacement propellers
2019-02-26 Added case build Pics
2019-02-28 Initial Schematic review
2019-03-02 Update SLA_1500_CAM
2019-03-03 Added SLA_1500_CAM_CONN
2019-03-04 Update SLA_1500_CAM_V2
2019-03-04 Update SLA 1500 CAM V2
2019-03-06 Create SOW pdf
2019-03-13 Create SLA_1500_CAM REV 3
2019-03-16 update SLA_CAM_V3
2019-03-19 Added Sunset DRU for EAGLE
2019-03-19 Update SLA1500_CAM REV 3.0
    Replaced vertical Molex connectors with right angle Molex connectors
2019-03-19 renamed file
2019-03-20 Update Schem and Brd
2019-03-24 Create SLA_1500_CAM_V4.s##
2019-03-24 Update SLA1500 CAM V4
2019-03-26 Update SLA1500 CAM
2019-03-27 Sunstone DRU
2019-04-03 Create SLA_1500_CAM_V5.s##
2019-04-03 Create SLA1500 CAM BOM V2
2019-04-04 Update SLA1500 CAM V6
2019-04-10 Update Library
2019-04-16 Update SLA1500 CAM V6
    Repositioned C16 and C18 coupling capacitors
2019-04-21 Create SLA1500_CAM_BOM_V7
2019-04-21 Create SLA1500_CAM_V7
2019-04-22 Update SLA1500CAM V7
2019-04-22 Update SLA1500CAM V6
2019-04-22 Create SLA1500CAM gerbers
2019-04-22 Update SLA1500 CAM V7
2019-04-22 Create Zipped Gerber Files
2019-04-22 Create SLA1500CAM_V7 zipped gerbers
2019-04-24 Update SLA1500CAM
2019-04-29 Create SLA1500CAM V8
2019-04-29 Update SLA1500CAM V8
2019-04-29 Create SLA1500CAM V8.fab
    This was created just for exporting FAB docs
2019-04-29 Created Fab drawings
2019-04-29 Rename SLA1500cam_fab
2019-05-05 Documentation
2019-05-05 Create SLA1500CAM Test xlsx
2019-05-08 Create Capstone Design Report
2019-05-13 Update Design Report
2019-05-13 Create .~lock.Poster1.odg#
2019-05-14 Update Poaster
2019-05-15 Update final documentation
2019-05-19 Update Poster
2019-05-22 Preflight Checklist, Operational Procedure, and System Config
2019-05-22 Added JST schem
2019-05-25 pics
2019-05-28 Create Poster2
2019-05-28 Update poster2
2019-05-29 Create SLA_1500_CAM_V8.b##
2019-05-29 Update Library/ Design Report
2019-05-29 Update Desing Report
2019-06-04 Update Docs
2019-06-07 Added Power Point
2019-06-11 Update final report
2019-06-12 final report

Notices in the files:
parts and their libraries:
SparkFun-Capacitors: Licensing: Creative Commons ShareAlike 4.0 International - https://creativecommons.org/licenses/by-sa/4.0
